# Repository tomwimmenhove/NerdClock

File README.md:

# NerdClock
7-Segment display using an LED and a 3-phase motor

See https://youtu.be/A6WD372-6BQ for a video of it running

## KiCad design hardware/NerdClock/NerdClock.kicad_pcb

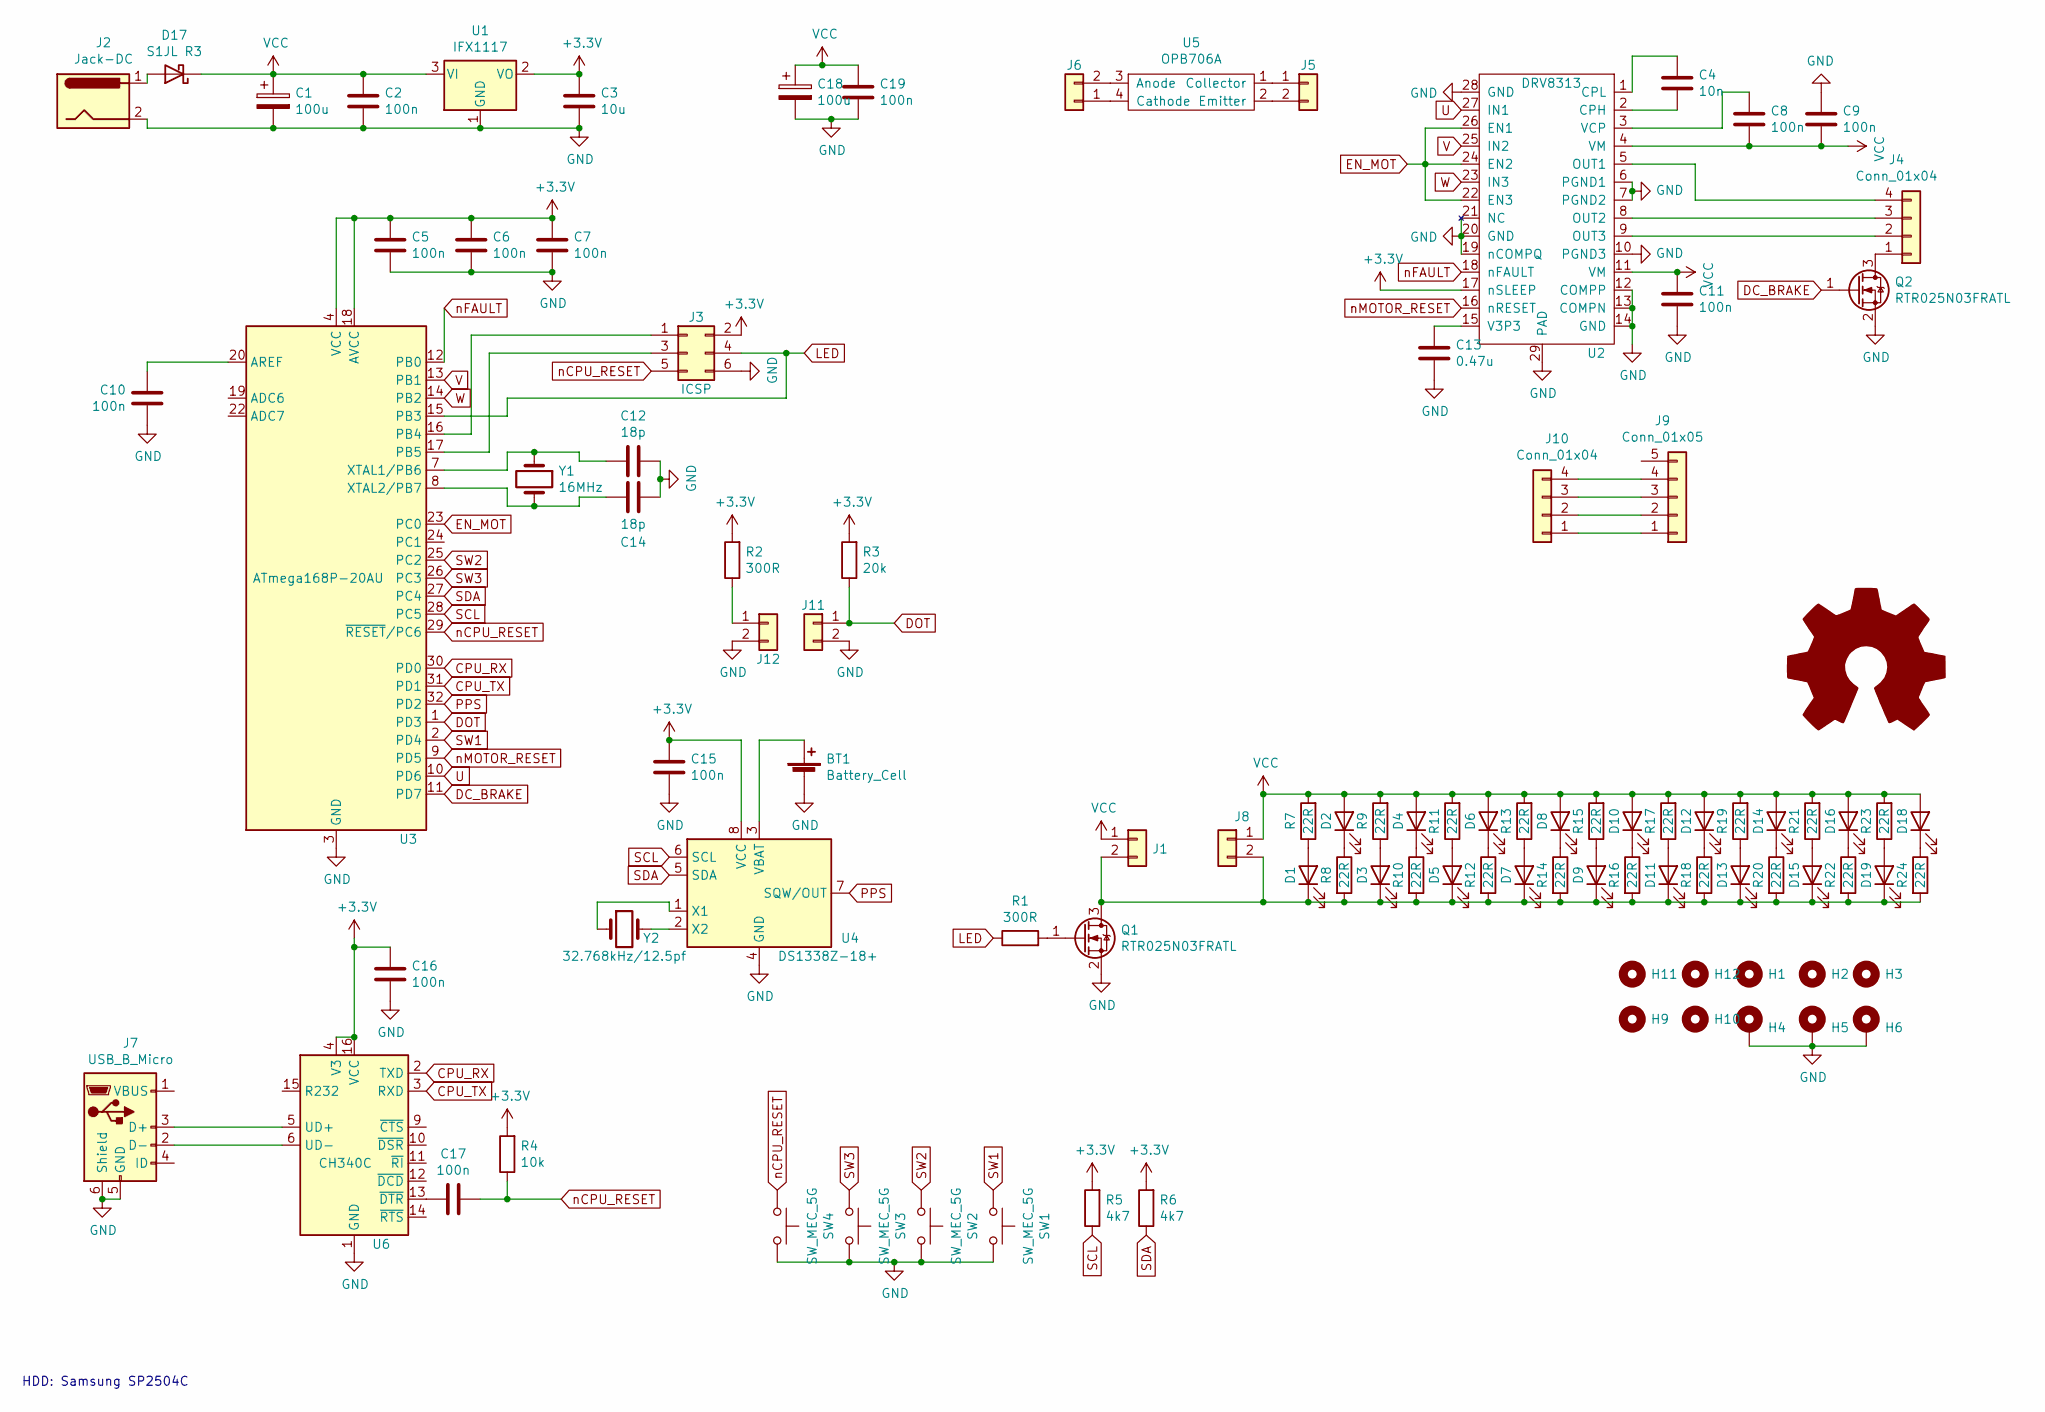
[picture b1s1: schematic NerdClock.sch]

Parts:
BT1: Battery_Cell; BatteryHolder_Keystone_1060_1x2032
C1, C18: 100u; CP_Elec_5x5.4
C2, C5, C6, C7, C8, C9, C10, C11, C15, C16, C17, C19: 100n; C_0603_1608Metric
C3: 10u; C_0603_1608Metric
C4: 10n; C_0603_1608Metric
C12, C14: 18p; C_0603_1608Metric
C13: 0.47u; C_0603_1608Metric
D1, D2, D3, D4, D5, D6, D7, D8, D9, D10, D11, D12, D13, D14, D15, D16, D18, D19: LED; WhiteLed1W
D17: S1JL R3; D_SMA
H1, H2, H3, H9, H10, H11, H12: MountingHole; MountingHole_3.2mm_M3
H4, H5, H6: MountingHole_Pad; MountingHole_3.2mm_M3_Pad_Via
J1, J5, J6, J11, J12: Conn_01x02; PinHeader_1x02_P2.54mm_Vertical
J2: Jack-DC; BarrelJack_Wuerth_6941xx301002
J3: ICSP; PinHeader_2x03_P2.54mm_Vertical
J4, J10: Conn_01x04; PinHeader_1x04_P2.54mm_Vertical
J7: USB_B_Micro; USB_Micro-B_Amphenol_10103594-0001LF_Horizontal
J8: Conn_01x02; PinHeader_2x01_P2.54mm_Vertical_SMD
J9: Conn_01x05; MotorConn
Q1, Q2: RTR025N03FRATL; SOT-23
R1, R2: 300R; R_0603_1608Metric
R3: 20k; R_0603_1608Metric
R4: 10k; R_0603_1608Metric
R5, R6: 4k7; R_0603_1608Metric
R7, R8, R9, R10, R11, R12, R13, R14, R15, R16, R17, R18, R19, R20, R21, R22, R23, R24: 22R; R_0603_1608Metric
SW1, SW2, SW3, SW4: SW_MEC_5G; SW_SPST_Omron_B3FS-100xP
U1: IFX1117; SOT-223-3_TabPin2
U2: DRV8313; HTSSOP-28-1EP_4.4x9.7mm_P0.65mm_EP3.4x9.5mm_ThermalVias
U3: ATmega168P-20AU; TQFP-32_7x7mm_P0.8mm
U4: DS1338Z-18+; SOIC-8_3.9x4.9mm_P1.27mm
U5: OPB706A
U6: CH340C; SOIC-16_3.9x9.9mm_P1.27mm
Y1: 16MHz; Crystal_SMD_ECS_CSM3X-2Pin_7.6x4.1mm
Y2: 32.768kHz/12.5pf; Crystal_C26-LF_D2.1mm_L6.5mm_Horizontal

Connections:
+3V3: C3.1, C5.1, C6.1, C7.1, C15.1, C16.1, J3.2, R2.2, R3.2, R4.2, R5.2, R6.2, U1.2 (VO), U2.17 (nSLEEP), U3.4 (VCC), U3.6 (VCC), U3.18 (AVCC), U4.8 (VCC), U6.4 (V3), U6.16 (VCC)
CPU_RX: U3.30 (PD0), U6.2 (TXD)
CPU_TX: U3.31 (PD1), U6.3 (RXD)
DC_BRAKE: Q2.1 (G), U3.11 (PD7)
DOT: J11.1, R3.1, U3.1 (PD3)
EN_MOT: U2.22 (EN3), U2.24 (EN2), U2.26 (EN1), U3.23 (PC0)
GND: BT1.2 (-), C1.2, C2.2, C3.2, C5.2, C6.2, C7.2, C9.1, C10.1, C11.2, C12.2, C13.2, C14.2, C15.2, C16.2, C18.2, C19.2, H4.1, H5.1, H6.1, J2.2, J3.6, J7.5 (GND), J7.6 (Shield), J11.2, J12.2, Q1.2 (S), Q2.2 (S), SW1.3 (B), SW1.4 (B), SW2.3 (B), SW2.4 (B), SW3.3 (B), SW3.4 (B), SW4.3 (B), SW4.4 (B), U1.1 (GND), U2.6 (PGND1), U2.7 (PGND2), U2.10 (PGND3), U2.12 (COMPP), U2.13 (COMPN), U2.14 (GND), U2.19 (nCOMPQ), U2.20 (GND), U2.21 (NC), U2.28 (GND), U2.29 (PAD), U3.3 (GND), U3.5 (GND), U3.21 (GND), U4.4 (GND), U6.1 (GND)
LED: J3.4, R1.1, U3.15 (PB3)
unnamed: BT1.1 (+), U4.3 (VBAT)
unnamed: C4.1, U2.1 (CPL)
unnamed: C4.2, U2.2 (CPH)
unnamed: C8.1, U2.3 (VCP)
unnamed: C10.2, U3.20 (AREF)
unnamed: C12.1, U3.7 (XTAL1/PB6), Y1.1
unnamed: C13.1, U2.15 (V3P3)
unnamed: C14.1, U3.8 (XTAL2/PB7), Y1.2
unnamed: C17.2, U6.13 (~DTR)
unnamed: D1.1 (K), D3.1 (K), D5.1 (K), D7.1 (K), D9.1 (K), D11.1 (K), D13.1 (K), D15.1 (K), D19.1 (K), J1.2, J8.2, Q1.3 (D), R8.2, R10.2, R12.2, R14.2, R16.2, R18.2, R20.2, R22.2, R24.2
unnamed: D1.2 (A), R7.1
unnamed: D2.1 (K), R8.1
unnamed: D3.2 (A), R9.1
unnamed: D4.1 (K), R10.1
unnamed: D5.2 (A), R11.1
unnamed: D6.1 (K), R12.1
unnamed: D7.2 (A), R13.1
unnamed: D8.1 (K), R14.1
unnamed: D9.2 (A), R15.1
unnamed: D10.1 (K), R16.1
unnamed: D11.2 (A), R17.1
unnamed: D12.1 (K), R18.1
unnamed: D13.2 (A), R19.1
unnamed: D14.1 (K), R20.1
unnamed: D15.2 (A), R21.1
unnamed: D16.1 (K), R22.1
unnamed: D17.2 (A), J2.1
unnamed: D18.1 (K), R24.1
unnamed: D19.2 (A), R23.1
unnamed: J3.1, U3.16 (PB4)
unnamed: J3.3, U3.17 (PB5)
unnamed: J4.1, Q2.3 (D)
unnamed: J4.2, U2.9 (OUT3)
unnamed: J4.3, U2.8 (OUT2)
unnamed: J4.4, U2.5 (OUT1)
unnamed: J5.1, U5.1 (Collector)
unnamed: J5.2, U5.2 (Emitter)
unnamed: J6.1, U5.4 (Cathode)
unnamed: J6.2, U5.3 (Anode)
unnamed: J7.2 (D-), U6.6 (UD-)
unnamed: J7.3 (D+), U6.5 (UD+)
unnamed: J9.1, J10.1
unnamed: J9.2, J10.2
unnamed: J9.3, J10.3
unnamed: J9.4, J10.4
unnamed: J12.1, R2.1
unnamed: Q1.1 (G), R1.2
unnamed: U4.1 (X1), Y2.1
unnamed: U4.2 (X2), Y2.2
PPS: U3.32 (PD2), U4.7 (SQW/OUT)
SCL: R5.1, U3.28 (PC5), U4.6 (SCL)
SDA: R6.1, U3.27 (PC4), U4.5 (SDA)
SW1: SW1.1 (A), SW1.2 (A), U3.2 (PD4)
SW2: SW2.1 (A), SW2.2 (A), U3.25 (PC2)
SW3: SW3.1 (A), SW3.2 (A), U3.26 (PC3)
U: U2.27 (IN1), U3.10 (PD6)
V: U2.25 (IN2), U3.13 (PB1)
VCC: C1.1, C2.1, C8.2, C9.2, C11.1, C18.1, C19.1, D2.2 (A), D4.2 (A), D6.2 (A), D8.2 (A), D10.2 (A), D12.2 (A), D14.2 (A), D16.2 (A), D17.1 (K), D18.2 (A), J1.1, J8.1, R7.2, R9.2, R11.2, R13.2, R15.2, R17.2, R19.2, R21.2, R23.2, U1.3 (VI), U2.4 (VM), U2.11 (VM)
W: U2.23 (IN3), U3.14 (PB2)
nCPU_RESET: C17.1, J3.5, R4.1, SW4.1 (A), SW4.2 (A), U3.29 (~RESET~/PC6)
nFAULT: U2.18 (nFAULT), U3.12 (PB0)
nMOTOR_RESET: U2.16 (nRESET), U3.9 (PD5)

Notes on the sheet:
HDD: Samsung SP2504C

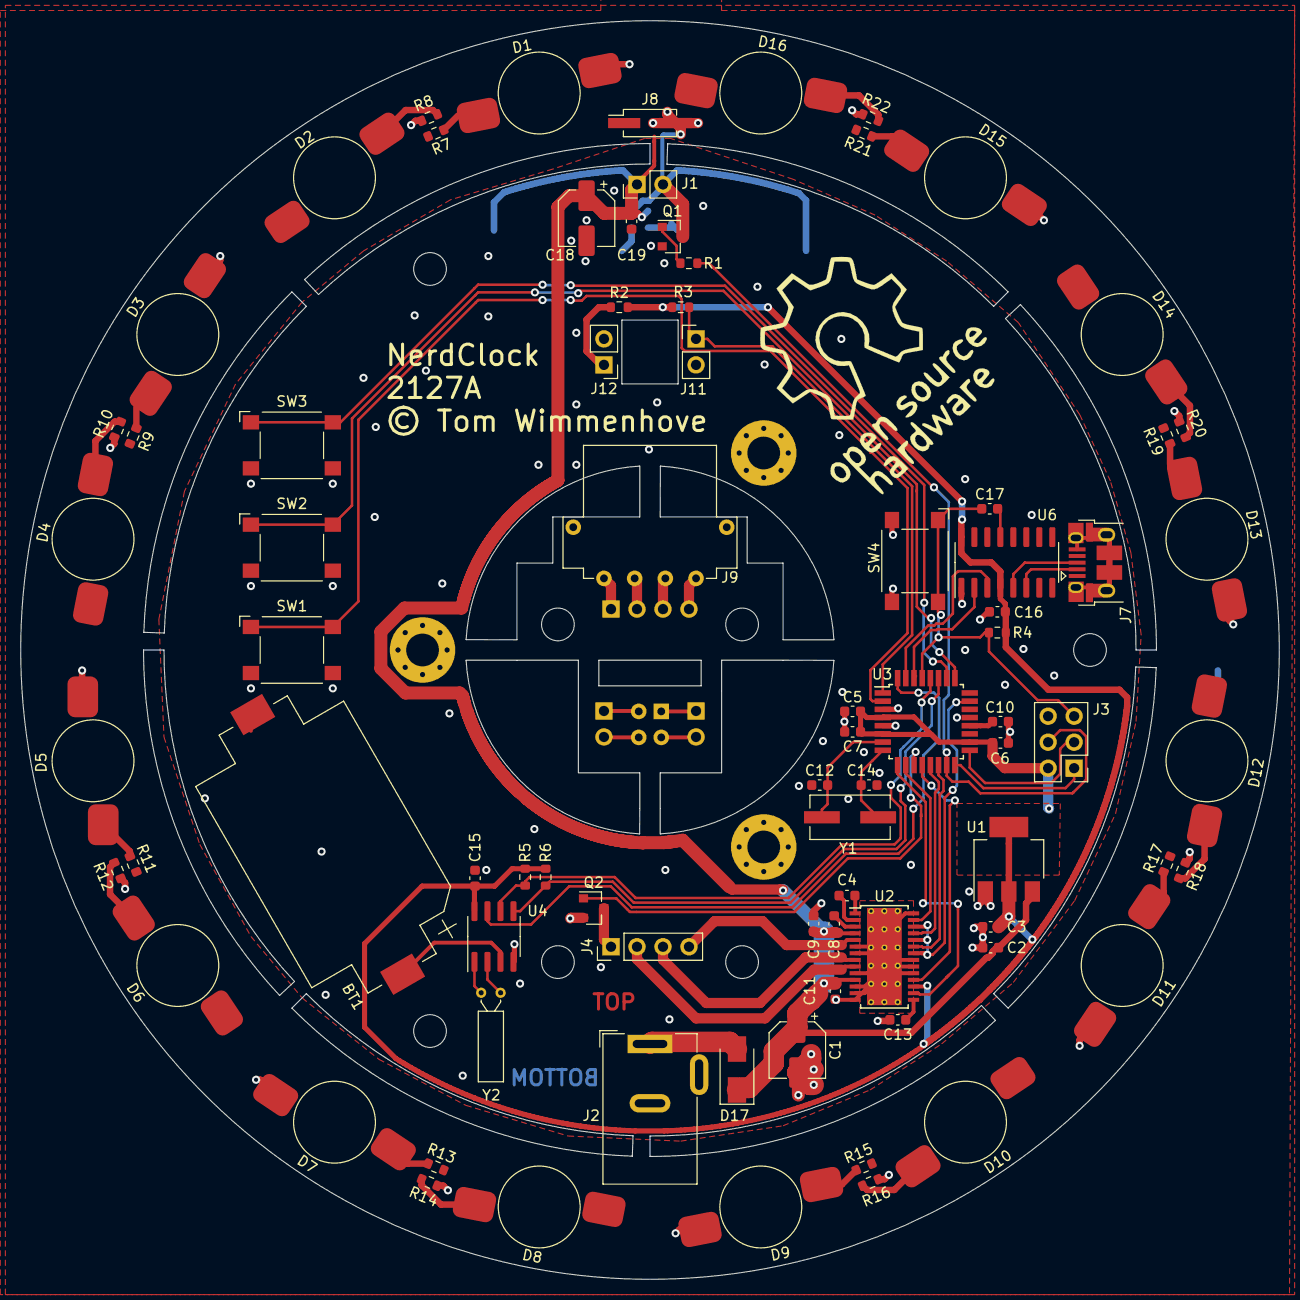
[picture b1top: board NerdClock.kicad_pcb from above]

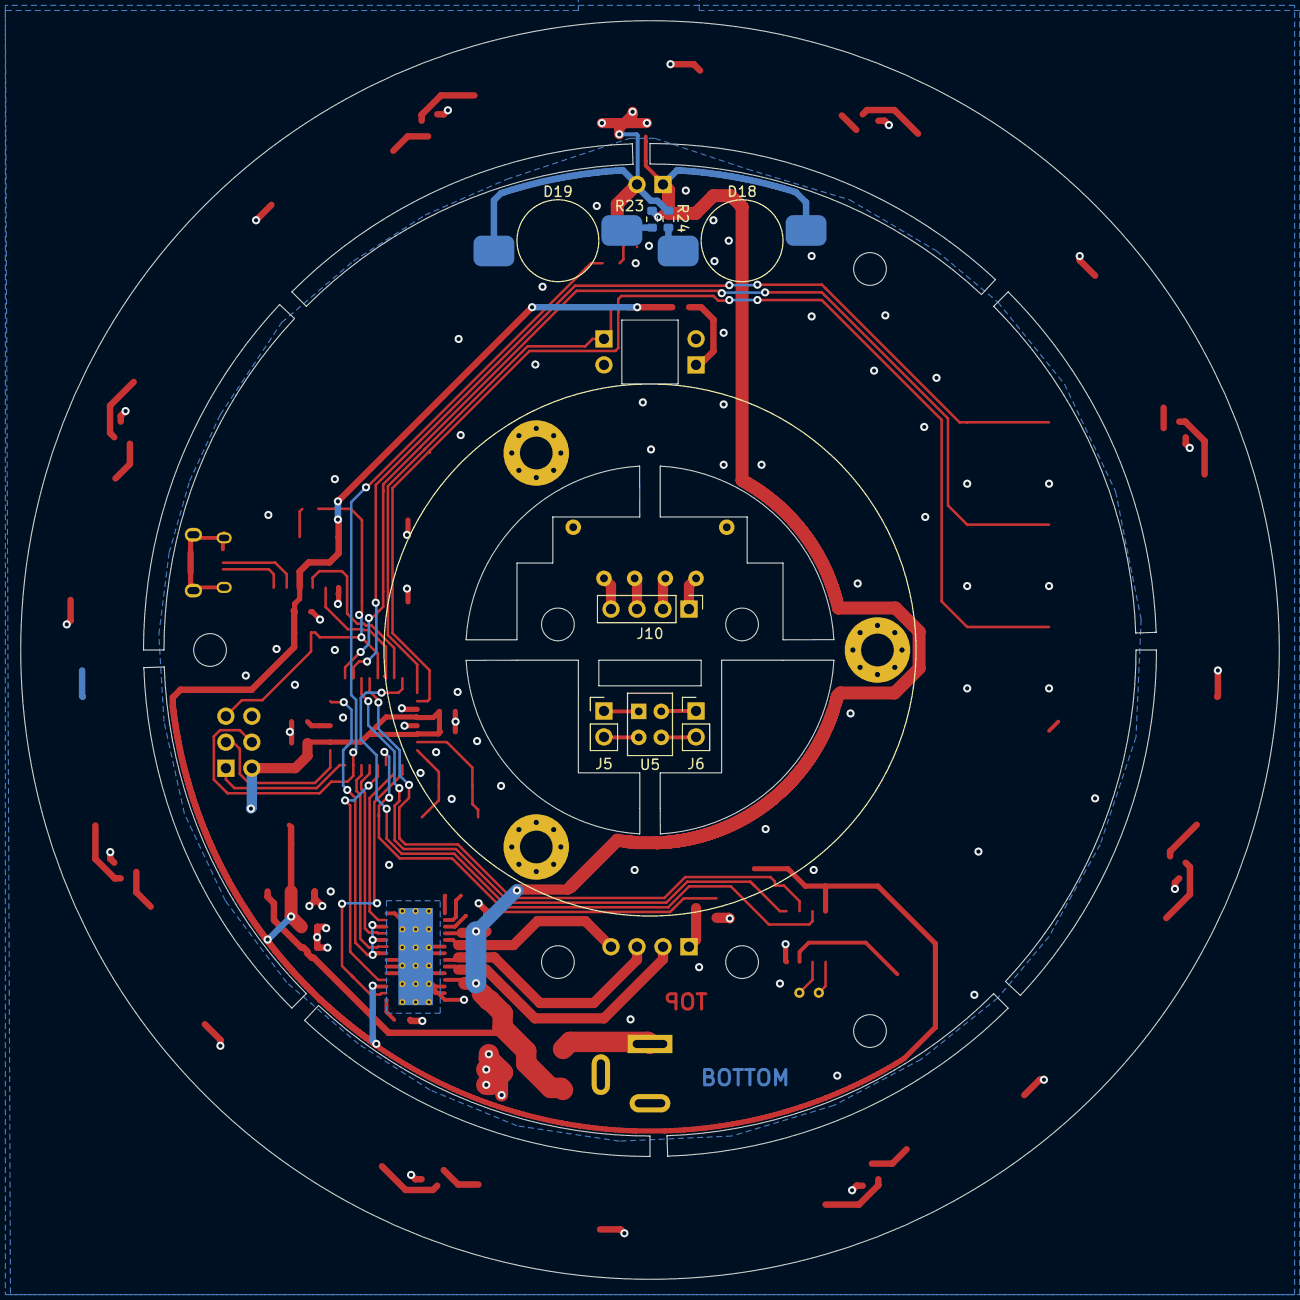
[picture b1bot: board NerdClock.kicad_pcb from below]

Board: 2 copper layers, 123.0 x 123.0 mm, 99 parts (8 on the bottom side), 70 nets.

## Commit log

2021-07-05 WIP: separated 3-phase stuff
2021-07-05 Simple internal timekeeping
2021-07-05 Removed build files
2021-07-05 Undo jiffies shit
2021-07-06 Harder, faster, better
2021-07-06 backup
2021-07-07 Ramping in ISR
2021-07-08 Photo sensor keeps track of platters
2021-07-08 Added readme and licence
2021-07-09 Added LICENCE
2021-07-09 Minor Cleanup
2021-07-10 Added initial schemtaic
2021-07-11 Added breakout tabs
2021-07-11 Put LEDs on the right side (wtffff)
2021-07-11 Routing backup
2021-07-11 Routing probably done?
2021-07-12 Fix all DRC errors
2021-07-12 Removed excessive vias and change battery angle
2021-07-12 Simplified code
2021-07-13 Added untested RTC code
2021-07-13 Added serial console
2021-07-15 RTC comm works
2021-07-16 Off to JLCPCB!
2021-07-23 Fixed hardware bug (polarity of IR led in relfection sensor
2021-07-23 Cleanup and stopepd using Tick to combat jitter
2021-07-24 DId we finally fix the fucking jitter?!
2021-07-25 Fixed resistor value
2021-07-25 Rotate with buttons.
2021-07-25 Added my dumb helper tools
2021-09-11 WIP: create digit-pattern image in code. First ugly result
2021-09-11 WIP: create digit-pattern image in code. Print "1234"
2021-09-12 Added PCB clock face
2021-10-02 Some changes to disk pattern
2021-10-02 Set the time using the buttons

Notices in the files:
hardware/NerdClock/NerdClock.kicad_pcb:
© Tom Wimmenhove
